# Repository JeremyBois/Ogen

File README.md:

# Ogen
A PMW3360 breakout board based on [this](https://www.tindie.com/products/jkicklighter/pmw3360-motion-sensor/).

 ## Changelog
 * 11/11/2022: Initial update to V1.2. This board is now ready for JLCPCB SMT assembly service:
   - Replace linear voltage regulator : from [TLV70019](https://jlcpcb.com/partdetail/TexasInstruments-TLV70019DDCR/C2862411) (out of stock) to [VRH1902LTX](https://jlcpcb.com/partdetail/Anasem-VRH1902LTX/C697975) (in stock)
   - Add metadata to each part to enable generation of BOM / POS using [this plugin](https://github.com/bennymeg/JLC-Plugin-for-KiCad)
 * 23/06/2022: Initial update to V1.1. Changed the 5 1-bit shift registers to 3 2-bit ones. Slightly shrunk board. New logo (very important).
 * 04/10/2020: Fixed major flaw in PMW3360 footprint.
 * 30/09/2020: Initial commit.

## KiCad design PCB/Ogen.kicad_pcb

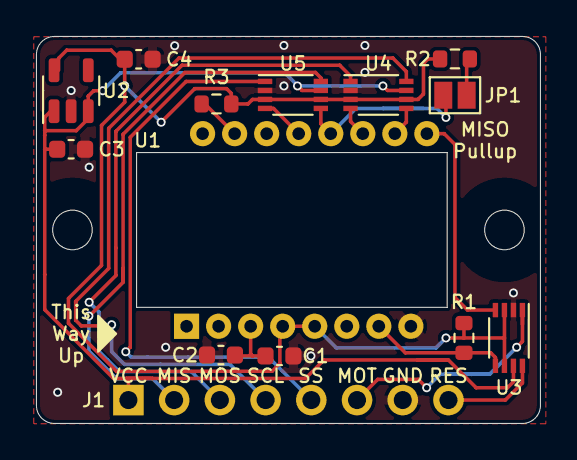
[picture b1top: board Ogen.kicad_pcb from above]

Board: 2 copper layers, 28.0 x 21.5 mm, 17 parts (1 on the bottom side), 18 nets.

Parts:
A1: Art; Ariamelon_Logo
C1: 4.7uF; C_0603_1608Metric
C2: 100nF; C_0603_1608Metric
C3, C4: 1uF; C_0603_1608Metric
H1, H2: M2; MountingHole_2.2mm_M2
J1: Input; PinHeader_1x08_P2.54mm_Vertical
JP1: Jumper; SolderJumper-2_P1.3mm_Open_Pad1.0x1.5mm
R1, R2: 10k; R_0603_1608Metric
R3: 39R; R_0603_1608Metric
U1: PMW3360DM-T2QU; IC_PMW3360DM-T2QU
U2: VRH1902LTX; SOT-23-5
U3, U4, U5: TXS0102DCU; VSSOP-8_2.3x2mm_P0.5mm

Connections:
GND: C1.2, C2.2, C3.2, C4.2, J1.7, U1.8 (GND), U2.2 (GND), U3.2 (GND), U4.2 (GND), U5.2 (GND)
MISO: JP1.2 (B), U1.12 (MISO), U5.5 (A1)
MISO-H: J1.2, U5.8 (B1)
MOSI: U1.11 (MOSI), U4.4 (A2)
MOSI-H: J1.3, U4.1 (B2)
MOT: U1.9 (MOTION), U3.4 (A2)
MOT-H: J1.6, U3.1 (B2)
NRESET: R1.1, U1.7 (NRESET), U3.5 (A1)
NRESET-H: J1.8, U3.8 (B1)
unnamed: C1.1, C2.1, U1.3 (VDDPIX)
unnamed: JP1.1 (A), R2.1
unnamed: R3.1, U1.15 (LED_P)
SCLK: U1.10 (SCLK), U4.5 (A1)
SCLK-H: J1.4, U4.8 (B1)
SS: U1.13 (NCS), U5.4 (A2)
SS-H: J1.5, U5.1 (B2)
VCC: C3.1, J1.1, U2.1 (IN), U2.3 (EN), U3.7 (VCCB), U4.7 (VCCB), U5.7 (VCCB)
VDD: C4.1, R1.2, R2.2, R3.2, U1.4 (VDD), U1.5 (VDDIO), U2.5 (OUT), U3.3 (VCCA), U3.6 (OE), U4.3 (VCCA), U4.6 (OE), U5.3 (VCCA), U5.6 (OE)

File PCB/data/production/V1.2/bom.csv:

Comment,Designator,Footprint,LCSC Part #,Quantity
4.7uF,C1,C_0603_1608Metric,C19666,1
100nF,C2,C_0603_1608Metric,C14663,1
1uF,"C3, C4",C_0603_1608Metric,C15849,2
10k,"R1, R2",R_0603_1608Metric,C25804,2
39R,R3,R_0603_1608Metric,C227492,1
PMW3360DM-T2QU,U1,IC_PMW3360DM-T2QU,,1
VRH1902LTX,U2,SOT-23-5,C697975,1
TXS0102DCU,"U3, U4, U5",VSSOP-8_2.3x2mm_P0.5mm,C53434,3

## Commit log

2022-11-11 🚚 - Move V1.1 gerbers to corresponding folder.
2022-11-11 🍱 - Add datasheet for both PMW3360DM sensor and Linear voltage regulator.
2022-11-11 ✨ ♻️ - Add metadata required to generate BOM and POS files for JLCPCB SMT assembly service (can use Fabrication Toolkit plugin to generate up to date BOM and POS). Add description to PCB and schema f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
2022-11-11 🍱 - Generate production ready files for JLCPCB manufacturing and assembly.
2022-11-11 📝 🍱 - Update schematic and bump to version V1.2. Update changelog accordingly.
2022-11-11 🙈 - Add gerber temp folder to gitignore.
